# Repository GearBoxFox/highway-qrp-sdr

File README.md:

# highway-qrp-sdr
 A 5W CW transciever built off the RP2350 MCU. Built for Hackclub Highway!

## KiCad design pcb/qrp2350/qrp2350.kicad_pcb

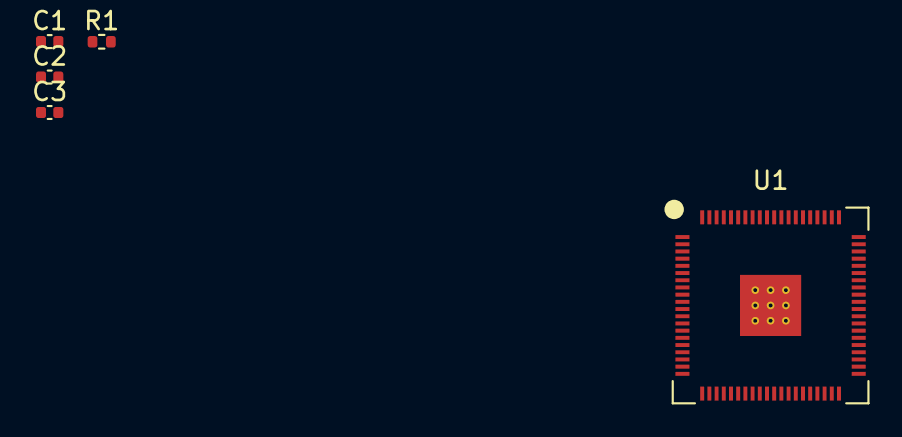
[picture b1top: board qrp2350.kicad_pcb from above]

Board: 2 copper layers, 5 parts (0 on the bottom side), 4 nets, no tracks yet.

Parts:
C1, C2, C3: 4.7u; C_0402_1005Metric
R1: 33; R_0402_1005Metric
U1: RP2350B-QFN80; RP2350B_QFN-80_EP_10.573x10.573_Pitch0.4mm

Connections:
+1V1: C2.1, U1.65 (VREG_FB)
+3.3V: C1.1, R1.1, U1.64 (VREG_VIN)
GND: C1.2, C2.2, C3.2, U1.62 (VREG_PGND)
unnamed: C3.1, R1.2, U1.61 (VREG_AVDD)

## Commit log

2025-05-15 added block diagram image
2025-05-15 added planning to journal
2025-05-15 started pcb schematic
2025-05-15 update to start using full rpi pico 2
2025-05-24 5/24/25
2025-05-29 created transmitter side stuff
2025-07-10 AHHHH
